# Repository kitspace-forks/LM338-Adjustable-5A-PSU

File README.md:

# LM338 1.8V-30V 5A Linear PSU

This repository contains EagleCAD PCB files for a 5 Amp adjustable voltage linear power supply using the LM338 IC. Output is adjustable between 1.8V and 30V; the input voltage must be at least 5V above the desired output voltage. Theoretically the design is capable of up to 150 watts power, but the LM338 will require proper cooling.

This design is based on the _Adjustable Regulator With Improved Ripple Rejection_ design found on page 18 of the Texas Instruments LM338 [datasheet](http://www.ti.com/lit/ds/symlink/lm338.pdf).

This work was originally created in 2013 but is now being published here under the MIT licence.

## More Information

See: https://devtty.io/2017/09/electronics/lm338-linear-voltage-regulator-pcb/

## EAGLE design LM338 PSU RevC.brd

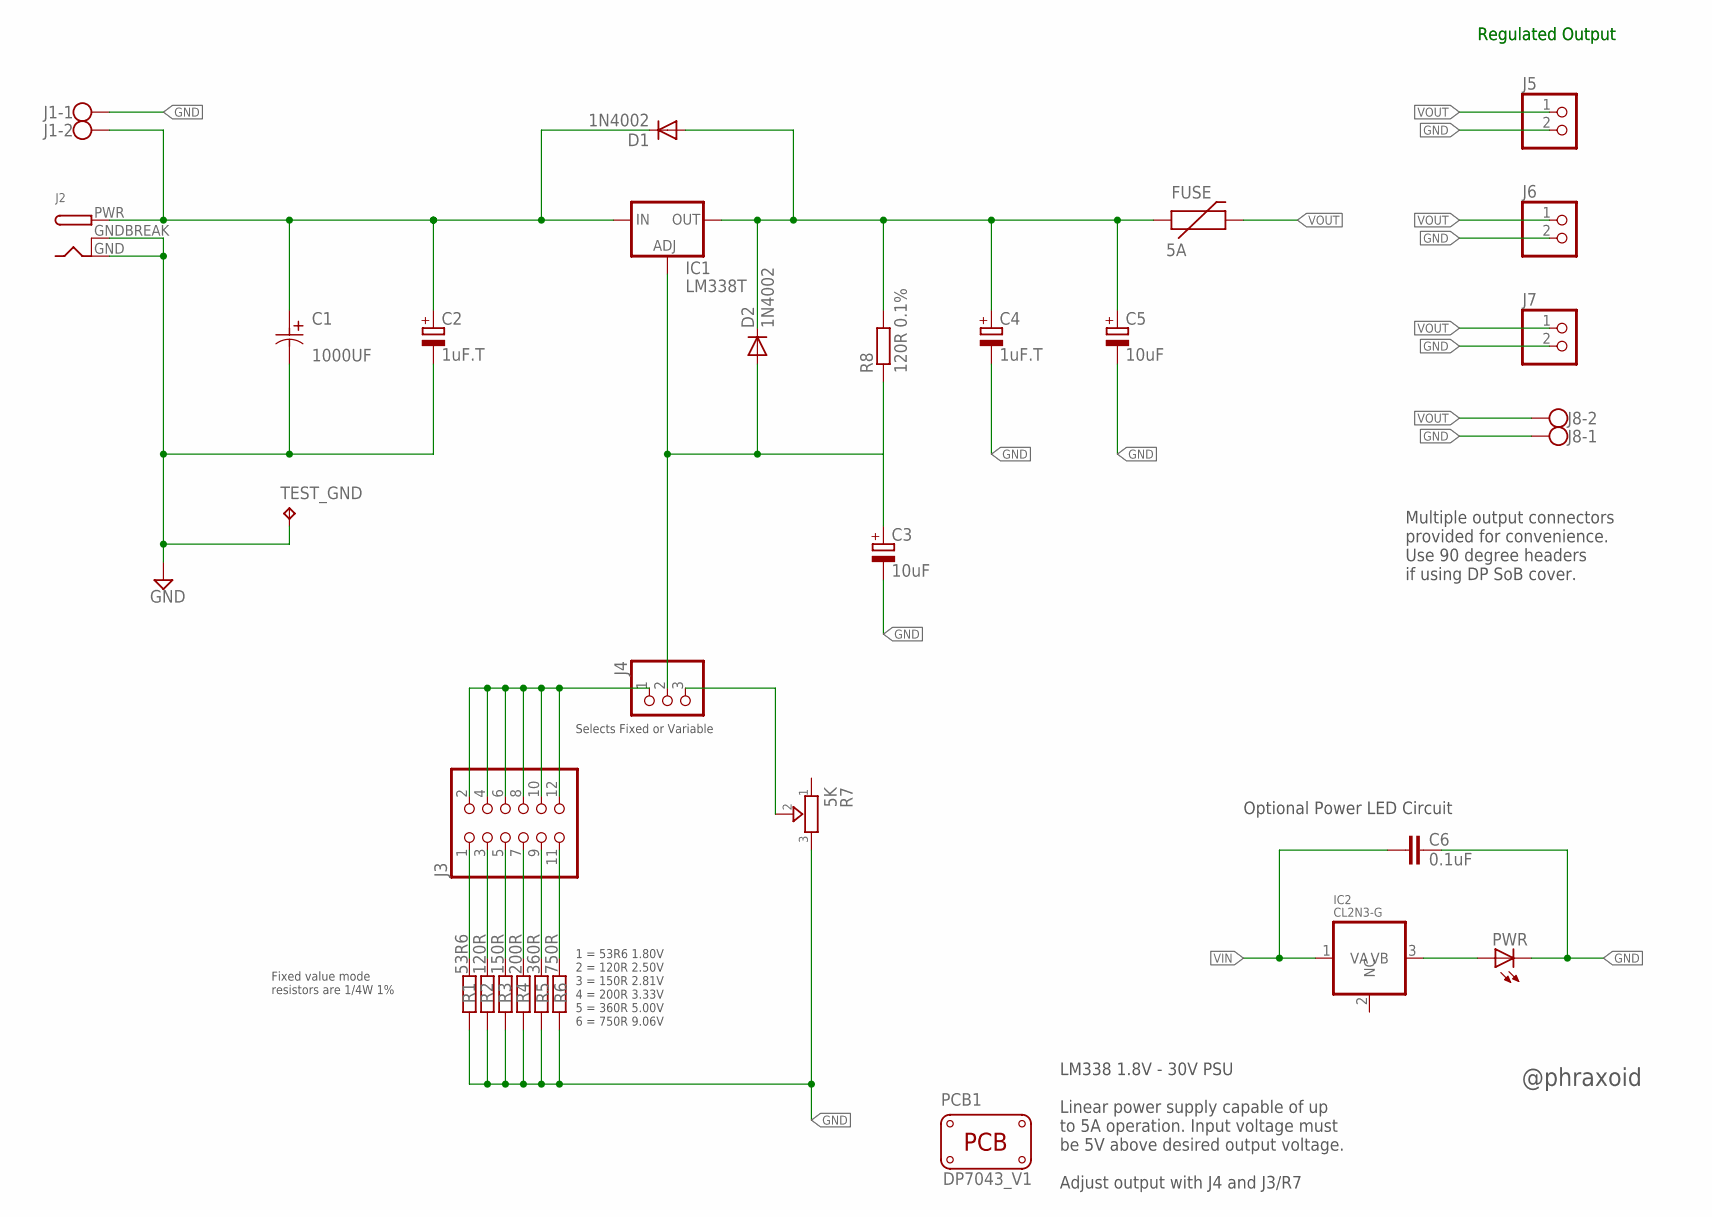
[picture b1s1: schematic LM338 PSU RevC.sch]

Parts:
C1: 1000UF; CAPPR500-1250X2500; MPN ECA1HM102
C2, C4: 1uF.T; E5-4
C3, C5: 10uF; E2,5-7; MPN ECEA1HN100U
C6: 0.1uF; C025-025X050; MPN 02016D104KAT2A
D1, D2: 1N4002; DO41-10; MPN 1N4002RLG
FUSE: 5A; PTC; MPN 30R400UF
IC1: LM338T; TO220-ADJ; MPN LM338T/NOPB
IC2: CL2N3-G; TO-92
J1, J8: W237-102; MPN MC000048
J2: DCBARRELPTH; DCJACK_2MM_PTH
J3: PINHD-2X6; 2X06
J4: PINHD-1X3/90; 1X03/90; MPN MC34747
J5, J6, J7: PINHD-1X2/90; 1X02/90; MPN MC34745
PCB1: PCB_DP_RECTANGLE-43X70; DP7043_V1
PWR: LED5MM; MPN C503B-RBN-CX0Y0AA1
R1: 53R6; 0207/10; MPN H853R6BYA
R2: 120R; 0207/10; MPN PR5Y-120RBI
R3: 150R; 0207/10; MPN H8150RBYA
R4: 200R; 0207/10; MPN H8200RBYA
R5: 360R; 0207/10; MPN MF25 360R
R6: 750R; 0207/10; MPN H8750RBYA
R7: 5K; TRIMMER_3362P; MPN 3362P-1-502LF
R8: 120R 0.1%; 0207/10; MPN MF25 120R
TEST_GND: TPPAD1-13; P1-13

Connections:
ADJ: C3.+, D2.A, IC1.ADJ, J4.2, R8.1
GND: C1.2, C2.-, C3.-, C4.-, C5.-, C6.2, J1.1, J2.GND, J2.GNDBREAK, J5.2, J6.2, J7.2, J8.1, PWR.K (C), R1.1, R2.1, R3.1, R4.1, R5.1, R6.1, R7.3, TEST_GND.TP
unnamed: J3.2, J3.4, J3.6, J3.8, J3.10, J3.12, J4.1
unnamed: J4.3, R7.2
unnamed: J3.1, R1.2
unnamed: J3.3, R2.2
unnamed: J3.5, R3.2
unnamed: J3.7, R4.2
unnamed: J3.9, R5.2
unnamed: J3.11, R6.2
unnamed: IC2.3 (VB), PWR.A
OUT: C4.+, C5.+, D1.A, D2.C, FUSE.P$1 (1), IC1.OUT, R8.2
VIN: C1.1, C2.+, C6.1, D1.C, IC1.IN, IC2.1 (VA), J1.2, J2.PWR
VOUT: FUSE.P$2 (2), J5.1, J6.1, J7.1, J8.2

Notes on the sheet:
Regulated Output
Multiple output connectors provided for convenience. Use 90 degree headers if using DP SoB cover.
1 = 53R6 1.80V 2 = 120R 2.50V 3 = 150R 2.81V 4 = 200R 3.33V 5 = 360R 5.00V 6 = 750R 9.06V
Fixed value mode resistors are 1/4W 1%
LM338 1.8V - 30V PSU Linear power supply capable of up to 5A operation. Input voltage must be 5V above desired output voltage. Adjust output with J4 and J3/R7
@phraxoid
Optional Power LED Circuit
Selects Fixed or Variable

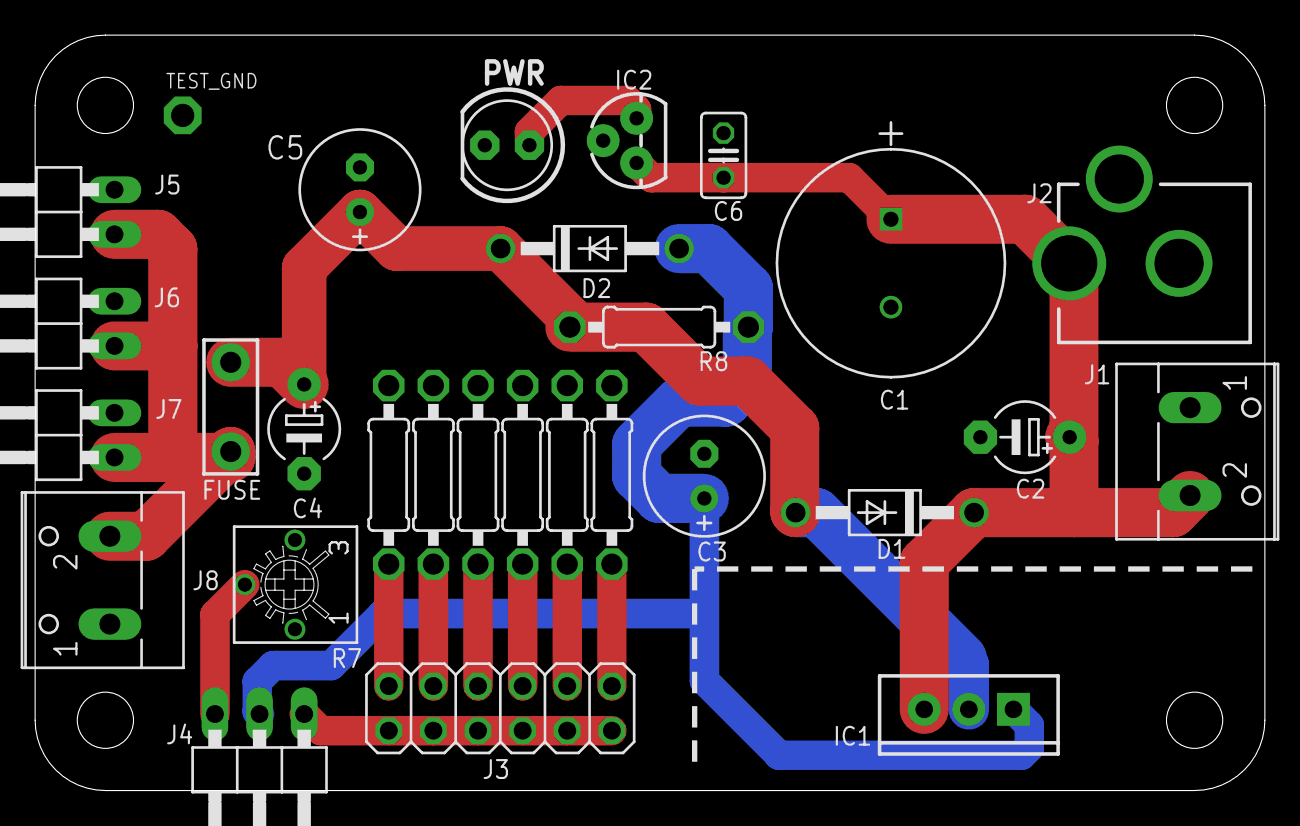
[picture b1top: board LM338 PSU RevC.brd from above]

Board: 2 copper layers, 70.0 x 43.0 mm, 30 parts (0 on the bottom side), 14 nets.

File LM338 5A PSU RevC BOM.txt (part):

Partlist exported from D:/My Documents/Documents/Electronics/EAGLE/Project Files/PCB002 - LM338 PSU/RevC/LM338 PSU RevC.sch at 03/09/2017 09:27

Part     Value                  Device                 Package            Description                                         MF                           MPN                OC_FARNELL OC_NEWARK PACKAGE        PCB_SIZE  SUPPLIER  TOLERANCE TP_SIGNAL_NAME VALUE  VOLTAGERATING
C1       1000UF                 ECA1HHG102-D12.5XP5    CAPPR500-1250X2500 Aluminum Electrolytic Capacitors/Radial Lead Type   PANASONIC                    ECA1HM102          9693823    96K9163   Radial Lead-TH           PANASONIC ±20 %                    1000UF 50V          
C2       1uF.T                  CPOL-EUE5-4            E5-4               POLARIZED CAPACITOR, European symbol                                                                unknown                                                                                              
C3       10uF                   CPOL-EUE2.5-7          E2,5-7             POLARIZED CAPACITOR, European symbol                PANASONIC                    ECEA1HN100U        9696636                                                                                              
C4       1uF.T                  CPOL-EUE5-4            E5-4               POLARIZED CAPACITOR, European symbol                                                                unknown                                                                                              
C5       10uF                   CPOL-EUE2.5-7          E2,5-7             POLARIZED CAPACITOR, European symbol                PANASONIC                    ECEA1HN100U        9696636                                                                                              
C6       0.1uF                  C-EU025-025X050        C025-025X050       CAPACITOR, European symbol                          AVX                          02016D104KAT2A     1657913                                                                                              
D1       1N4002                 1N4004                 DO41-10            DIODE                                               ON SEMICONDUCTOR             1N4002RLG          1264225                                                                                              
D2       1N4002                 1N4004                 DO41-10            DIODE                                               ON SEMICONDUCTOR             1N4002RLG          1264225                                                                                              
FUSE     5A                     PTCPTH                 PTC                Resettable Fuse PTC                                 LITTELFUSE                   30R400UF           1822241                                                                                              
IC1      LM338T                 V_REG_317SINK          TO220-ADJ          Voltage Regulator                                   TEXAS INSTRUMENTS            LM338T/NOPB        1469094                                                                                              
IC2      CL2N3-G                CL2N3-G                TO-92                                                                                                                  unknown                                                                                              
J1                              W237-102               W237-102           WAGO SCREW CLAMP                                    MULTICOMP                    MC000048           2008019    70K9898                                                                                   
J2                              DCBARRELPTH            DCJACK_2MM_PTH     2.0mm DC Barrel Jack                                                                                unknown                                                                                              
J3                              PINHD-2X6              2X06               PIN HEADER                                                                                          unknown                                                                                              
J4                              PINHD-1X3/90           1X03/90            PIN HEADER                                          MULTICOMP                    MC34747            1593427                                                                                              
J5                              PINHD-1X2/90           1X02/90            PIN HEADER                                          MULTICOMP                    MC34745            1593426                                                                                              
J6                              PINHD-1X2/90           1X02/90            PIN HEADER                                          MULTICOMP                    MC34745            1593426                                                                                              
J7                              PINHD-1X2/90           1X02/90            PIN HEADER                                          MULTICOMP                    MC34745            1593426                                                                                              
J8                              W237-102               W237-102           WAGO SCREW CLAMP                                    MULTICOMP                    MC000048           2008019    70K9898                                                                                   
PCB1     PCB_DP_RECTANGLE-43X70 PCB_DP_RECTANGLE-43X70 DP7043_V1          Dangerous Prototypes Standard Rectangular PCB sizes                                                 unknown                             DP7043_V1                                                        
PWR                             LED5MM                 LED5MM             LED                                                 CREE                         C503B-RBN-CX0Y0AA1 1855569                                                                                              
R1       53R6                   R-EU_0207/10           0207/10            RESISTOR, European symbol                           TE CONNECTIVITY / HOLSWORTHY H853R6BYA          1751303                                                                                              
R2       120R                   R-EU_0207/10           0207/10            RESISTOR, European symbol                           WELWYN                       PR5Y-120RBI        1634027                                                                                              
R3       150R                   R-EU_0207/10           0207/10            RESISTOR, European symbol                           TE CONNECTIVITY / HOLSWORTHY H8150RBYA          1751336                                                                                              
R4       200R                   R-EU_0207/10           0207/10            RESISTOR, European symbol                           TE CONNECTIVITY / HOLSWORTHY H8200RBYA          1751365                                                                                              
R5       360R                   R-EU_0207/10           0207/10            RESISTOR, European symbol                           MULTICOMP                    MF25 360R          9341790                                                                                              
R6       750R                   R-EU_0207/10           0207/10            RESISTOR, European symbol                           TE CONNECTIVITY / HOLSWORTHY H8750RBYA          1751430                                                                                              
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
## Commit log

2017-09-03 Initial commit.
2017-09-03 Added README.md
2018-01-13 Update LICENSE

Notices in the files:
parts and their libraries:
SparkFun-PowerIC: Licensing: CC v3.0 Share-Alike You are welcome to use this library for commercial purposes.
